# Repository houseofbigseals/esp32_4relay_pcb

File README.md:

KOLOS is an automation module based on ESP32-S3, designed for remote control of laboratory equipment - AC devices, sensors, indicators. Designed to manage environmental control systems for laboratory greenhouses with higher plants.  

Designed on a 4-layer printed circuit board, has dimensions of 124x95 mm.  
Powered by 5V via USB-C or screw connector, it has built-in surge protection with a self-resetting fuse. ESP32 is powered by a built-in AMS-1117-3.3 stabilizer.  
The board has expansion pins for connecting additional equipment to the controller, as well as screw connectors for connecting sensors using the 1-Wire protocol. The firmware of the controller and communication with the PC is done through the built-in USB-UART converter CP2102N. The board contains four relay channels controlled via an optocoupler and an HDC1080 temperature-humidity sensor.  
Mounting can be done in the housing with M3 screws or on a DIN rail, for which fasteners are provided.  
The firmware is implemented on the basis of the ESP-HOME framework for integrating the product into the Home Assistant environment. The system is configured so that the user can securely access the board remotely, via a Wireguard network, or locally.  

The pcb contains:  
- 4 5v relay module
- buttons for manual switching of the relay state in an emergency situation  
- optocoupler for relay control from the controller
- AMS-1117-3.3.
- USB-UART converter CP2102N.
- USB type-c for power and connection to a PC
- expansion pins for ESP32
- temperature-humidity sensor HDC1080
- expansion pins for connecting sensors via 1-Wire

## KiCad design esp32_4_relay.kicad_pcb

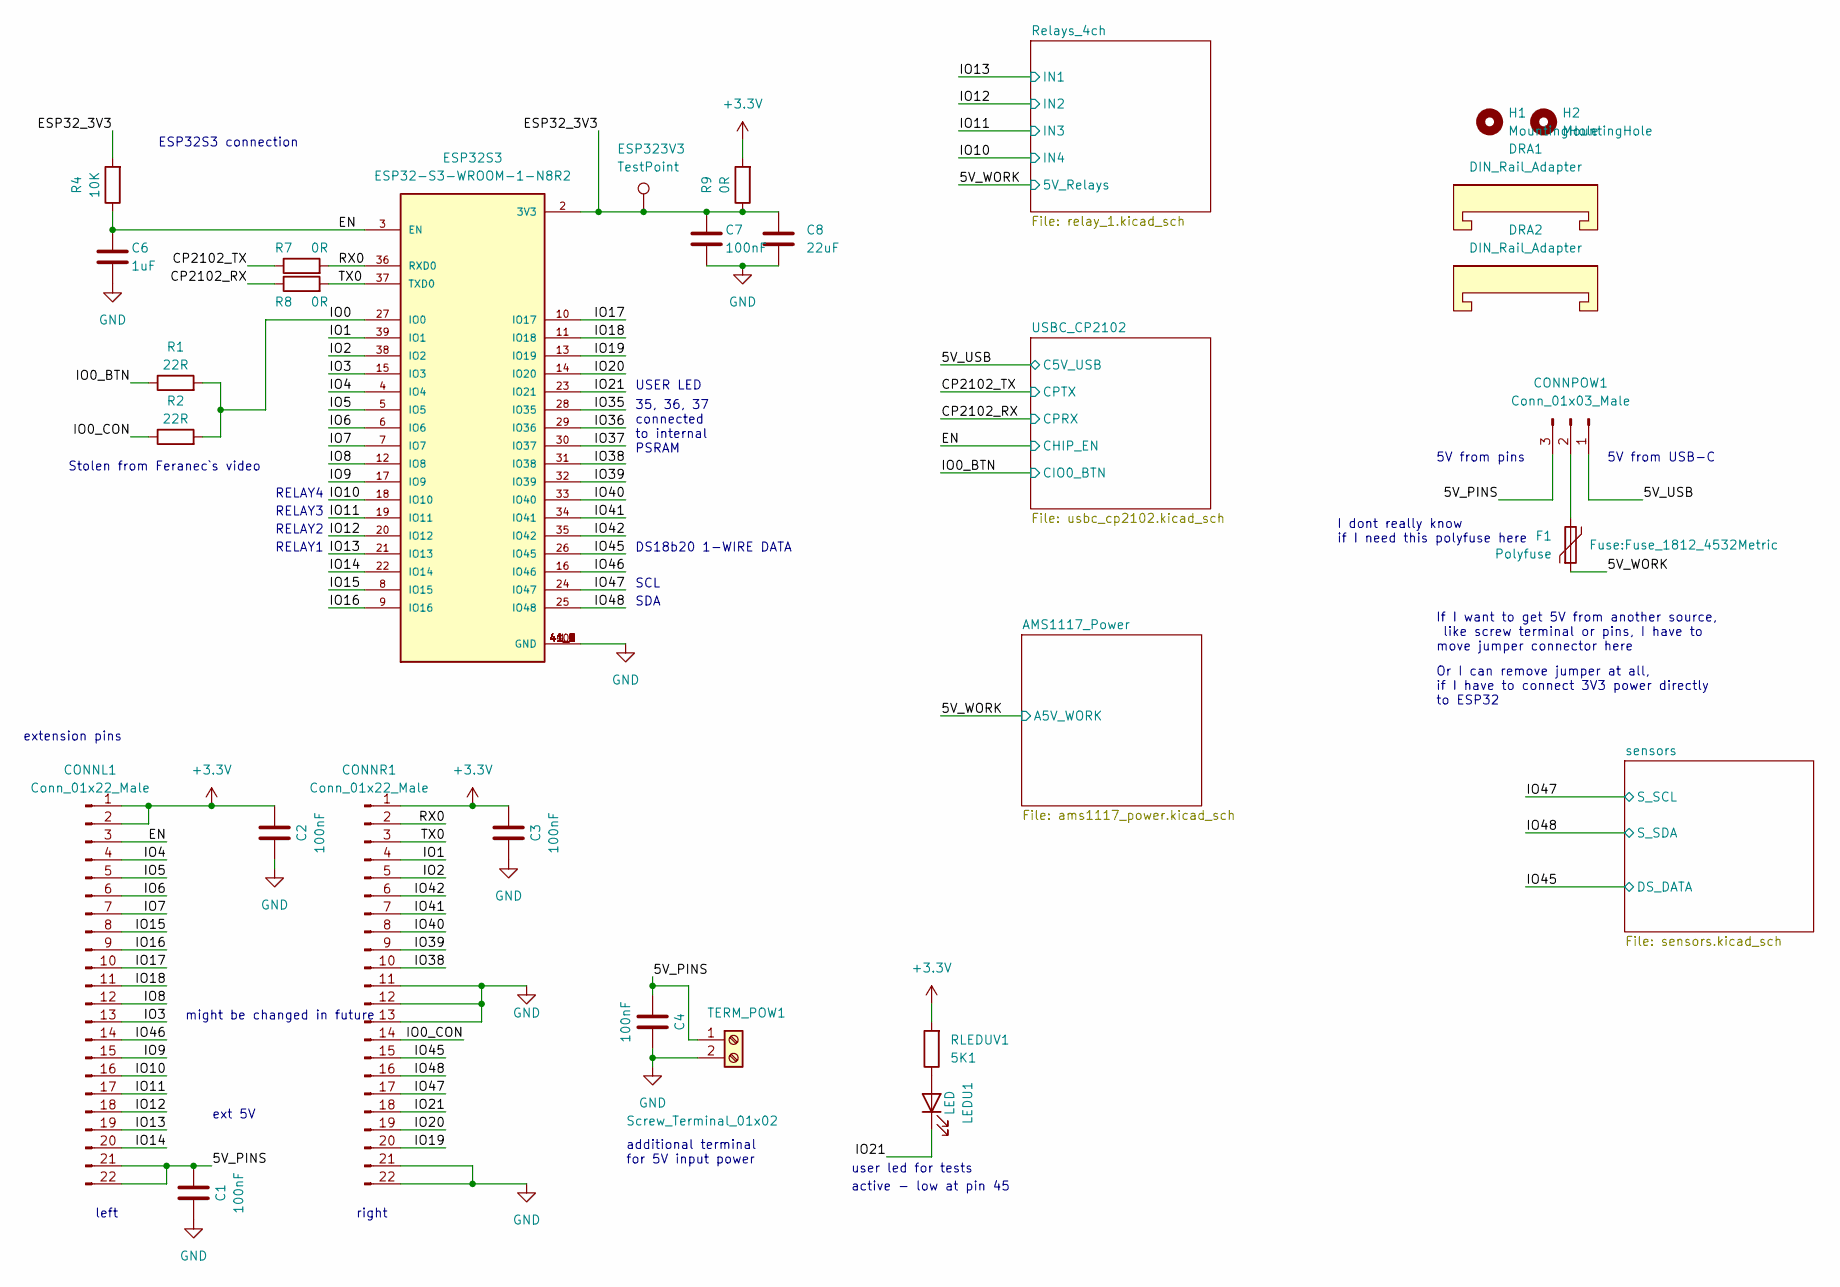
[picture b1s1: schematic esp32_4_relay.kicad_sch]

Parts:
C1, C2, C3, C4, C7: 100nF; C_0805_2012Metric
C6: 1uF; C_0805_2012Metric
C8: 22uF; C_0805_2012Metric
CONNL1: Conn_01x22_Male; PinHeader_1x22_P2.54mm_Vertical
CONNPOW1: Conn_01x03_Male; PinHeader_1x03_P2.54mm_Vertical
CONNR1: Conn_01x22_Male; PinHeader_1x22_P2.54mm_Vertical
DRA1, DRA2: DIN_Rail_Adapter; DINRailAdapter_3xM3_PhoenixContact_1201578
ESP32S3: ESP32-S3-WROOM-1-N8R2; XCVR_ESP32-S3-WROOM-1-N8R2; PARTREV v1.0; LCSC C2913204
ESP323V3: TestPoint; TestPoint_Pad_2.0x2.0mm
F1: Polyfuse; Fuse_1812_4532Metric; LCSC C84140
H1, H2: MountingHole; MountingHole_3.2mm_M3_DIN965
LEDU1: LED; LED_0805_2012Metric
R1, R2: 22R; R_0805_2012Metric
R4: 10K; R_0805_2012Metric
R7, R8, R9: 0R; R_0805_2012Metric
RLEDUV1: 5K1; R_0805_2012Metric
TERM_POW1: Screw_Terminal_01x02; Screw-2-pin-conn

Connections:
+3.3V: C2.2, C3.2, CONNL1.1, CONNL1.2, CONNR1.1, R9.2, RLEDUV1.2; also elsewhere on the board
/5V_PINS: C1.2, C4.2, CONNL1.21, CONNL1.22, CONNPOW1.3, TERM_POW1.1
/5V_USB: CONNPOW1.1; also elsewhere on the board
/5V_WORK: F1.1; also elsewhere on the board
/CP2102_RX: R8.1; also elsewhere on the board
/CP2102_TX: R7.1; also elsewhere on the board
/EN: C6.1, CONNL1.3, ESP32S3.3 (EN), R4.1; also elsewhere on the board
/ESP32_3V3: C7.1, C8.1, ESP32S3.2 (3V3), ESP323V3.1, R4.2, R9.1
/IO0: ESP32S3.27 (IO0), R1.2, R2.2
/IO0_BTN: R1.1; also elsewhere on the board
/IO0_CON: CONNR1.14, R2.1
/IO1: CONNR1.4, ESP32S3.39 (IO1)
/IO2: CONNR1.5, ESP32S3.38 (IO2)
/IO3: CONNL1.13, ESP32S3.15 (IO3)
/IO4: CONNL1.4, ESP32S3.4 (IO4)
/IO5: CONNL1.5, ESP32S3.5 (IO5)
/IO6: CONNL1.6, ESP32S3.6 (IO6)
/IO7: CONNL1.7, ESP32S3.7 (IO7)
/IO8: CONNL1.12, ESP32S3.12 (IO8)
/IO9: CONNL1.15, ESP32S3.17 (IO9)
/IO10: CONNL1.16, ESP32S3.18 (IO10); also elsewhere on the board
/IO11: CONNL1.17, ESP32S3.19 (IO11); also elsewhere on the board
/IO12: CONNL1.18, ESP32S3.20 (IO12); also elsewhere on the board
/IO13: CONNL1.19, ESP32S3.21 (IO13); also elsewhere on the board
/IO14: CONNL1.20, ESP32S3.22 (IO14)
/IO15: CONNL1.8, ESP32S3.8 (IO15)
/IO16: CONNL1.9, ESP32S3.9 (IO16)
/IO17: CONNL1.10, ESP32S3.10 (IO17)
/IO18: CONNL1.11, ESP32S3.11 (IO18)
/IO19: CONNR1.20, ESP32S3.13 (IO19)
/IO20: CONNR1.19, ESP32S3.14 (IO20)
/IO21: CONNR1.18, ESP32S3.23 (IO21), LEDU1.1 (K)
/IO35: ESP32S3.28 (IO35)
/IO36: ESP32S3.29 (IO36)
/IO37: ESP32S3.30 (IO37)
/IO38: CONNR1.10, ESP32S3.31 (IO38)
/IO39: CONNR1.9, ESP32S3.32 (IO39)
/IO40: CONNR1.8, ESP32S3.33 (IO40)
/IO41: CONNR1.7, ESP32S3.34 (IO41)
/IO42: CONNR1.6, ESP32S3.35 (IO42)
/IO45: CONNR1.15, ESP32S3.26 (IO45); also elsewhere on the board
/IO46: CONNL1.14, ESP32S3.16 (IO46)
/IO47: CONNR1.17, ESP32S3.24 (IO47); also elsewhere on the board
/IO48: CONNR1.16, ESP32S3.25 (IO48); also elsewhere on the board
/RX0: CONNR1.2, ESP32S3.36 (RXD0), R7.2
/TX0: CONNR1.3, ESP32S3.37 (TXD0), R8.2
GND: C1.1, C2.1, C3.1, C4.1, C6.2, C7.2, C8.2, CONNR1.11, CONNR1.12, CONNR1.13, CONNR1.21, CONNR1.22, ESP32S3.1 (GND), ESP32S3.40 (GND), ESP32S3.41_1 (GND), ESP32S3.41_2 (GND), ESP32S3.41_3 (GND), ESP32S3.41_4 (GND), ESP32S3.41_5 (GND), ESP32S3.41_6 (GND), ESP32S3.41_7 (GND), ESP32S3.41_8 (GND), ESP32S3.41_9 (GND), TERM_POW1.2; also elsewhere on the board
unnamed: CONNPOW1.2, F1.2
unnamed: LEDU1.2 (A), RLEDUV1.1

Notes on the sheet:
ESP32S3 connection
left
5V from pins
5V from USB-C
Or I can remove jumper at all, if I have to connect 3V3 power directly to ESP32
might be changed in future
extension pins
35, 36, 37 connected to internal PSRAM
user led for tests
SCL
SDA
ext 5V
I dont really know if I need this polyfuse here
USER LED
RELAY2
right
additional terminal for 5V input power
RELAY1
active - low at pin 45
RELAY4
DS18b20 1-WIRE DATA
Stolen from Feranec`s video
If I want to get 5V from another source, like screw terminal or pins, I have to move jumper connector here
RELAY3

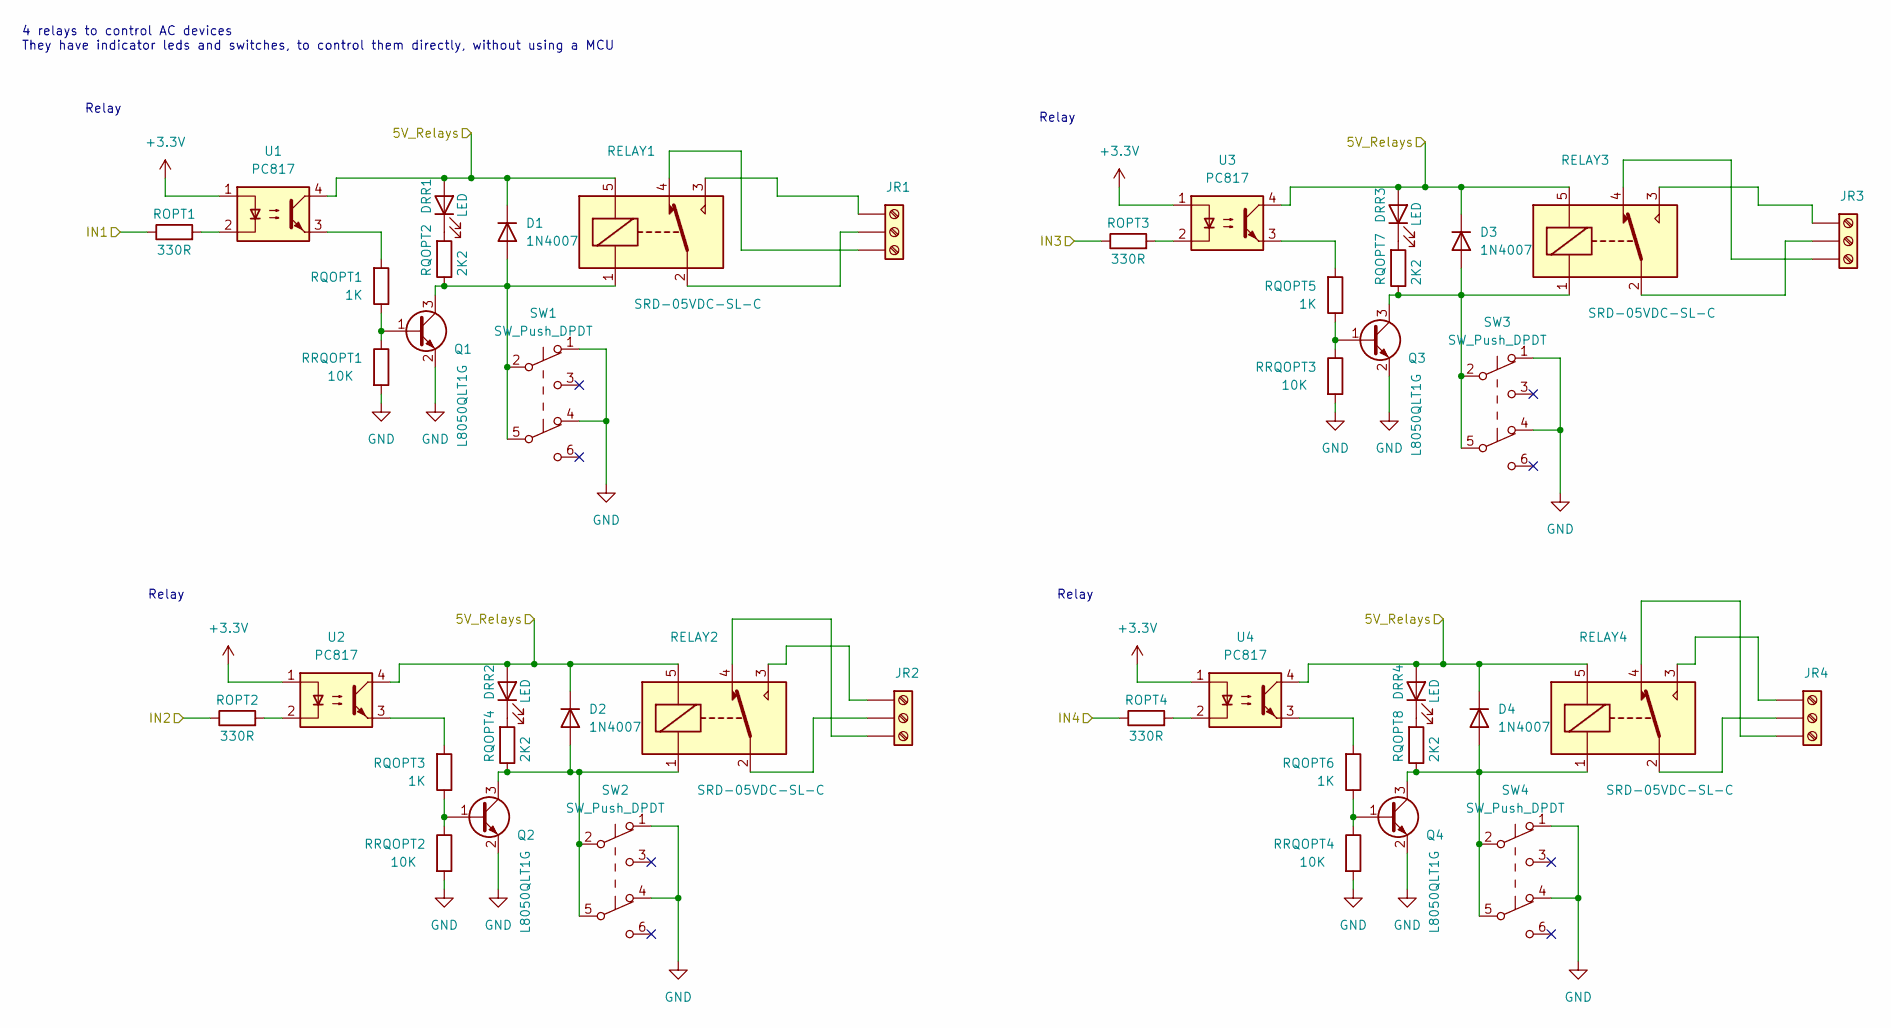
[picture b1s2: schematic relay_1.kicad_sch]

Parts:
D1, D2, D3, D4: 1N4007; D_SMA
DRR1, DRR2, DRR3, DRR4: LED; LED_0805_2012Metric
JR1, JR2, JR3, JR4: Screw_Terminal_01x03; Screw-3-pin-conn
Q1, Q2, Q3, Q4: L8050QLT1G; SOT-23
RELAY1, RELAY2, RELAY3, RELAY4: SRD-05VDC-SL-C; Relay_T75
ROPT1, ROPT2, ROPT3, ROPT4: 330R; R_0805_2012Metric
RQOPT1, RQOPT3, RQOPT5, RQOPT6: 1K; R_0805_2012Metric
RQOPT2, RQOPT4, RQOPT7, RQOPT8: 2K2; R_0805_2012Metric
RRQOPT1, RRQOPT2, RRQOPT3, RRQOPT4: 10K; R_0805_2012Metric
SW1, SW2, SW3, SW4: SW_Push_DPDT; switch-dpdt
U1, U2, U3, U4: PC817; SOP-4_3.8x4.1mm_P2.54mm

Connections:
+3.3V: U1.1, U2.1, U3.1, U4.1; also elsewhere on the board
/5V_WORK: D1.1 (K), D2.1 (K), D3.1 (K), D4.1 (K), DRR1.2 (A), DRR2.2 (A), DRR3.2 (A), DRR4.2 (A), RELAY1.5, RELAY2.5, RELAY3.5, RELAY4.5, U1.4, U2.4, U3.4, U4.4; also elsewhere on the board
/IO10: ROPT4.1; also elsewhere on the board
/IO11: ROPT3.1; also elsewhere on the board
/IO12: ROPT2.1; also elsewhere on the board
/IO13: ROPT1.1; also elsewhere on the board
GND: Q1.2 (E), Q2.2 (E), Q3.2 (E), Q4.2 (E), RRQOPT1.2, RRQOPT2.2, RRQOPT3.2, RRQOPT4.2, SW1.1 (A), SW1.4 (A), SW2.1 (A), SW2.4 (A), SW3.1 (A), SW3.4 (A), SW4.1 (A), SW4.4 (A); also elsewhere on the board
unnamed: D1.2 (A), Q1.3 (C), RELAY1.1, RQOPT2.1, SW1.2 (B), SW1.5 (B)
unnamed: D2.2 (A), Q2.3 (C), RELAY2.1, RQOPT4.1, SW2.2 (B), SW2.5 (B)
unnamed: D3.2 (A), Q3.3 (C), RELAY3.1, RQOPT7.1, SW3.2 (B), SW3.5 (B)
unnamed: D4.2 (A), Q4.3 (C), RELAY4.1, RQOPT8.1, SW4.2 (B), SW4.5 (B)
unnamed: DRR1.1 (K), RQOPT2.2
unnamed: DRR2.1 (K), RQOPT4.2
unnamed: DRR3.1 (K), RQOPT7.2
unnamed: DRR4.1 (K), RQOPT8.2
unnamed: JR1.1, RELAY1.3
unnamed: JR1.2, RELAY1.2
unnamed: JR1.3, RELAY1.4
unnamed: JR2.1, RELAY2.3
unnamed: JR2.2, RELAY2.2
unnamed: JR2.3, RELAY2.4
unnamed: JR3.1, RELAY3.3
unnamed: JR3.2, RELAY3.2
unnamed: JR3.3, RELAY3.4
unnamed: JR4.1, RELAY4.3
unnamed: JR4.2, RELAY4.2
unnamed: JR4.3, RELAY4.4
unnamed: Q1.1 (B), RQOPT1.1, RRQOPT1.1
unnamed: Q2.1 (B), RQOPT3.1, RRQOPT2.1
unnamed: Q3.1 (B), RQOPT5.1, RRQOPT3.1
unnamed: Q4.1 (B), RQOPT6.1, RRQOPT4.1
unnamed: ROPT1.2, U1.2
unnamed: ROPT2.2, U2.2
unnamed: ROPT3.2, U3.2
unnamed: ROPT4.2, U4.2
unnamed: RQOPT1.2, U1.3
unnamed: RQOPT3.2, U2.3
unnamed: RQOPT5.2, U3.3
unnamed: RQOPT6.2, U4.3

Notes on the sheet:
Relay
4 relays to control AC devices They have indicator leds and switches, to control them directly, without using a MCU

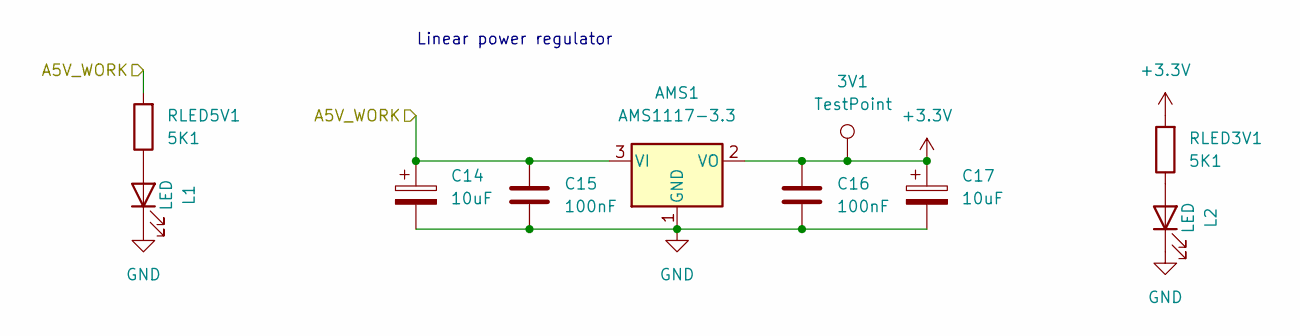
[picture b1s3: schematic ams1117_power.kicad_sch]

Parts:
3V1: TestPoint; TestPoint_Pad_2.0x2.0mm
AMS1: AMS1117-3.3; SOT-223-3_TabPin2
C14, C17: 10uF; CP_Radial_D10.0mm_P5.00mm
C15, C16: 100nF; C_0805_2012Metric
L1, L2: LED; LED_0805_2012Metric
RLED3V1, RLED5V1: 5K1; R_0805_2012Metric

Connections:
+3.3V: 3V1.1, AMS1.2 (VO), C16.1, C17.1, RLED3V1.2; also elsewhere on the board
/5V_WORK: AMS1.3 (VI), C14.1, C15.1, RLED5V1.2; also elsewhere on the board
GND: AMS1.1 (GND), C14.2, C15.2, C16.2, C17.2, L1.1 (K), L2.1 (K); also elsewhere on the board
unnamed: L1.2 (A), RLED5V1.1
unnamed: L2.2 (A), RLED3V1.1

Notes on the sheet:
Linear power regulator

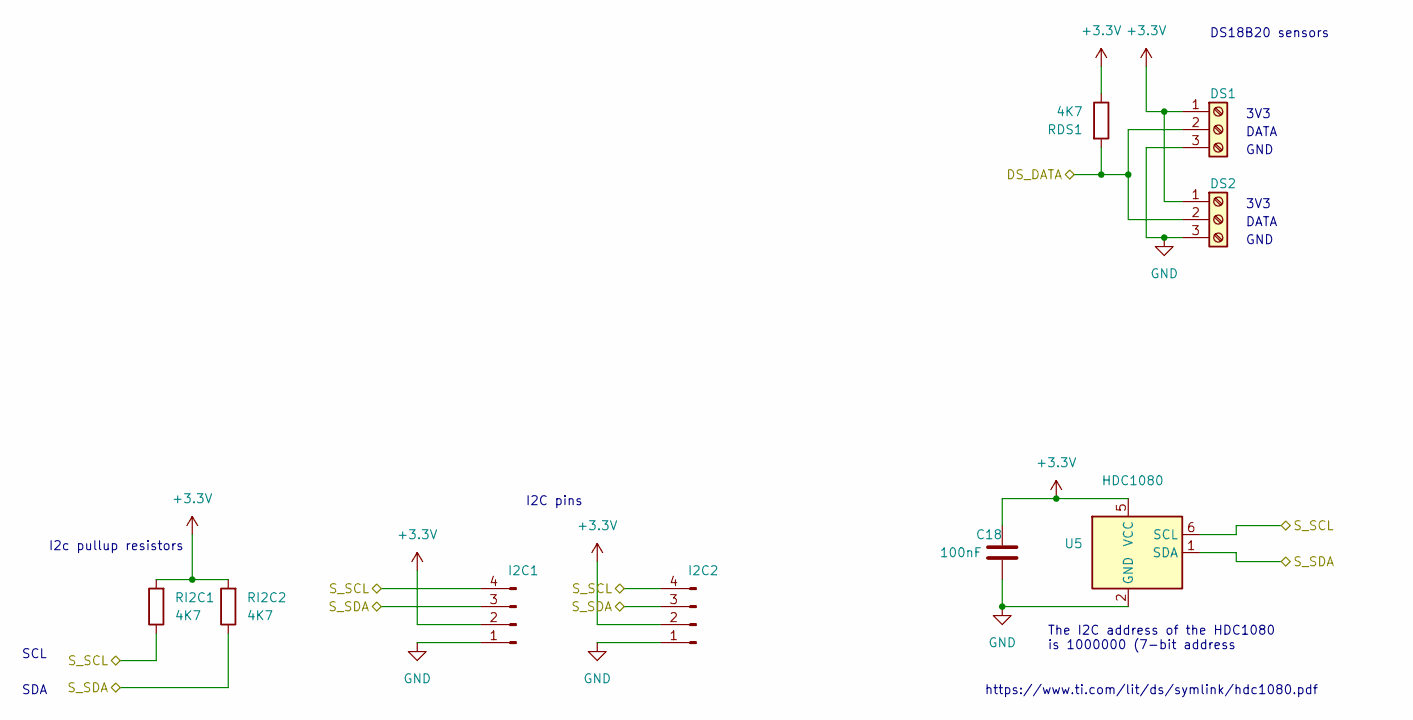
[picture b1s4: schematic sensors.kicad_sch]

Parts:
C18: 100nF; C_0805_2012Metric; LCSC C49678
DS1, DS2: Screw_Terminal_01x03; Screw-3-pin-conn
I2C1, I2C2: Conn_01x04_Male; PinHeader_1x04_P2.54mm_Vertical
RDS1: 4K7; R_0805_2012Metric
RI2C1, RI2C2: 4K7; R_0805_2012Metric
U5: HDC1080; Texas_PWSON-N6; LCSC C82227

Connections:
+3.3V: C18.1, DS1.1, DS2.1, I2C1.2, I2C2.2, RDS1.1, RI2C1.2, RI2C2.2, U5.5 (VCC); also elsewhere on the board
/IO45: DS1.2, DS2.2, RDS1.2; also elsewhere on the board
/IO47: I2C1.4, I2C2.4, RI2C1.1, U5.6 (SCL); also elsewhere on the board
/IO48: I2C1.3, I2C2.3, RI2C2.1, U5.1 (SDA); also elsewhere on the board
GND: C18.2, DS1.3, DS2.3, I2C1.1, I2C2.1, U5.2 (GND); also elsewhere on the board

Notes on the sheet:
GND
SCL
I2c pullup resistors
DATA
3V3
https://www.ti.com/lit/ds/symlink/hdc1080.pdf
I2C pins
SDA
The I2C address of the HDC1080 is 1000000 (7-bit address
DS18B20 sensors

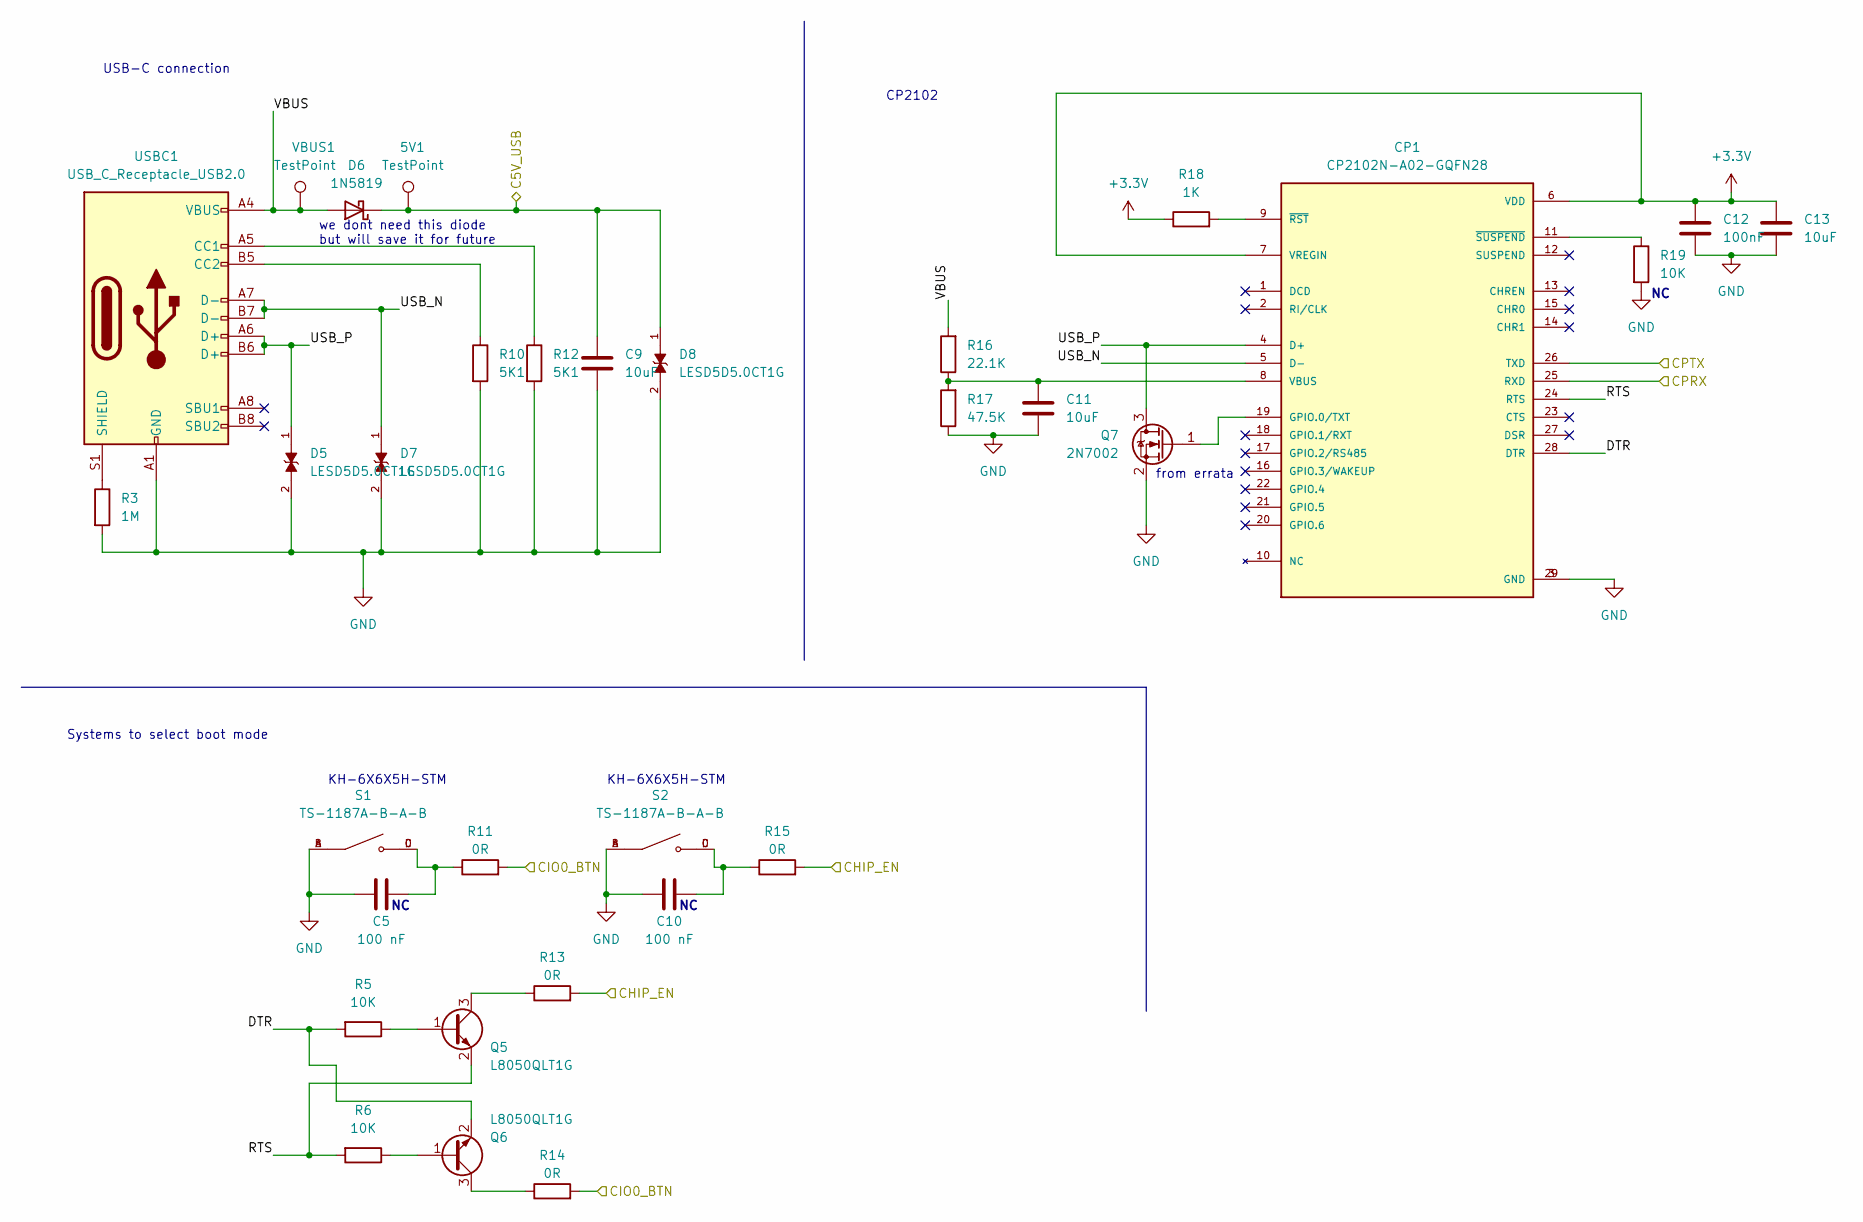
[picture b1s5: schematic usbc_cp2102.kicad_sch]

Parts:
5V1: TestPoint; TestPoint_Pad_2.0x2.0mm
C5, C10: 100 nF; C_0805_2012Metric
C9, C11, C13: 10uF; C_0805_2012Metric
C12: 100nF; C_0805_2012Metric
CP1: CP2102N-A02-GQFN28; QFN50P500X500X80-29N; PARTREV 1.5
D5, D7, D8: LESD5D5.0CT1G; TVS_LESD5D5.0CT1G; PARTREV O
D6: 1N5819; D_SMA
Q5, Q6: L8050QLT1G; SOT-23
Q7: 2N7002; SOT-23
R3: 1M; R_0805_2012Metric
R5, R6, R19: 10K; R_0805_2012Metric
R10, R12: 5K1; R_0805_2012Metric
R11, R13, R14, R15: 0R; R_0805_2012Metric
R16: 22.1K; R_0805_2012Metric
R17: 47.5K; R_0805_2012Metric
R18: 1K; R_0805_2012Metric
S1, S2: TS-1187A-B-A-B; SW_TS-1187A-B-A-B; PARTREV A0
USBC1: USB_C_Receptacle_USB2.0; USB_C_Receptacle_HRO_TYPE-C-31-M-12
VBUS1: TestPoint; TestPoint_Pad_2.0x2.0mm

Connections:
+3.3V: C12.1, C13.1, CP1.6 (VDD), CP1.7 (VREGIN), R18.1; also elsewhere on the board
/5V_USB: 5V1.1, C9.1, D6.1 (K), D8.1; also elsewhere on the board
/CP2102_RX: CP1.25 (RXD); also elsewhere on the board
/CP2102_TX: CP1.26 (TXD); also elsewhere on the board
/EN: R13.2, R15.2; also elsewhere on the board
/IO0_BTN: R11.2, R14.2; also elsewhere on the board
/USBC_CP2102/DTR: CP1.28 (DTR), Q6.2 (E), R5.2
/USBC_CP2102/RTS: CP1.24 (RTS), Q5.2 (E), R6.2
/USBC_CP2102/USB_N: CP1.5 (D-), D7.1, USBC1.A7 (D-), USBC1.B7 (D-)
/USBC_CP2102/USB_P: CP1.4 (D+), D5.1, Q7.3 (D), USBC1.A6 (D+), USBC1.B6 (D+)
/USBC_CP2102/VBUS: D6.2 (A), R16.2, USBC1.A4 (VBUS), USBC1.A9 (VBUS), USBC1.B4 (VBUS), USBC1.B9 (VBUS), VBUS1.1
GND: C5.1, C9.2, C10.1, C11.2, C12.2, C13.2, CP1.3 (GND), CP1.29 (GND), D5.2, D7.2, D8.2, Q7.2 (S), R3.2, R10.2, R12.2, R17.1, R19.2, S1.A, S1.B, S2.A, S2.B, USBC1.A1 (GND), USBC1.A12 (GND), USBC1.B1 (GND), USBC1.B12 (GND); also elsewhere on the board
unnamed: C5.2, R11.1, S1.C, S1.D
unnamed: C10.2, R15.1, S2.C, S2.D
unnamed: C11.1, CP1.8 (VBUS), R16.1, R17.2
unnamed: CP1.9 (~RST), R18.2
unnamed: CP1.11 (~SUSPEND), R19.1
unnamed: CP1.19 (GPIO.0/TXT), Q7.1 (G)
unnamed: Q5.1 (B), R5.1
unnamed: Q5.3 (C), R13.1
unnamed: Q6.1 (B), R6.1
unnamed: Q6.3 (C), R14.1
unnamed: R3.1, USBC1.S1 (SHIELD)
unnamed: R10.1, USBC1.B5 (CC2)
unnamed: R12.1, USBC1.A5 (CC1)

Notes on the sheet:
USB-C connection
KH-6X6X5H-STM
from errata
we dont need this diode but will save it for future
CP2102
Systems to select boot mode

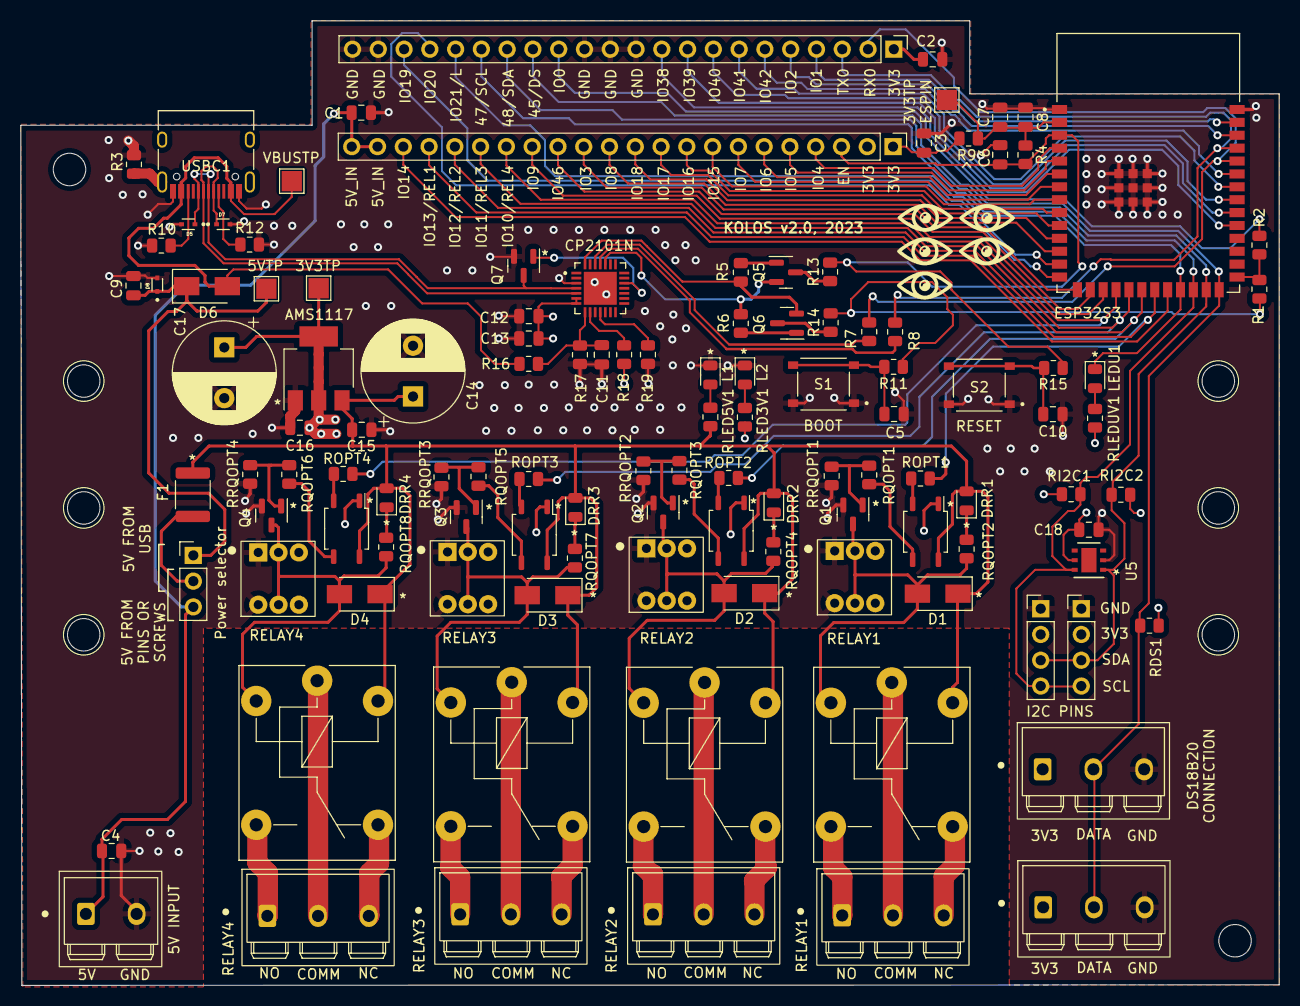
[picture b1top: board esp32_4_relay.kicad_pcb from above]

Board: 4 copper layers, 124.0 x 95.0 mm, 121 parts (0 on the bottom side), 98 nets.

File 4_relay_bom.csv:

Designator,Footprint,Quantity,Value,LCSC Part #
AMS1,SOT-223-3_TabPin2,1,AMS1117-3.3,C6186
"C1, C12, C15, C16, C18, C2, C3, C4, C7",805,9,100nF,C49678
"C11, C13, C9",805,3,10uF,C440198
C6,805,1,1uF,C28323
C8,805,1,22uF,C45783
CP1,QFN50P500X500X80-29N,1,CP2102N-A02-GQFN28,C964632
"D1, D2, D3, D4",D_SMA,4,1N4007,C95872
"D5, D7, D8",TVS_LESD5D5.0CT1G,3,LESD5D5.0CT1G,C383211
D6,D_SMA,1,1N5819,C191023
"DRR1, DRR2, DRR3, DRR4, L1, L2, LEDU1",805,7,LED,C84256
"DS1, DS2, JR1, JR2, JR3, JR4",Screw-3-pin-conn,6,Screw_Terminal_01x03,C784923
ESP32S3,XCVR_ESP32-S3-WROOM-1-N8R2,1,ESP32-S3-WROOM-1-N8R2,C2913204
F1,1812,1,Polyfuse,C84140
"Q1, Q2, Q3, Q4, Q5, Q6",SOT-23,6,L8050QLT1G,C8512 
Q7,SOT-23,1,2N7002,C8545
"R1, R2",805,2,22R,C17561
"R10, R12, RLED3V1, RLED5V1, RLEDUV1",805,5,5K1,C27834
"R11, R13, R14, R15, R7, R8, R9",805,7,0R,C17477
R16,805,1,22.1K,C17560
R17,805,1,47.5K,C17713
"R18, RQOPT1, RQOPT3, RQOPT5, RQOPT6",805,5,1K,C17513
R3,805,1,1M,C17514
"R4, R5, R6",805,3,10K,C17414
"RDS1, RI2C1, RI2C2",805,3,4K7,C17673
"RELAY1, RELAY2, RELAY3, RELAY4",Relay_T75,4,SRD-05VDC-SL-C,C35449
"ROPT1, ROPT2, ROPT3, ROPT4",805,4,330R,C17630
"RQOPT2, RQOPT4, RQOPT7, RQOPT8",805,4,2K2,C17520
"S1, S2",SW_TS-1187A-B-A-B,2,TS-1187A-B-A-B,C318884
"SW1, SW2, SW3, SW4",switch-dpdt,4,SW_Push_DPDT,C318862
TERM_POW1,Screw-2-pin-conn,1,Screw_Terminal_01x02,C784922
"U1, U2, U3, U4",SOP-4_3.8x4.1mm_P2.54mm,4,PC817,C6649
U5,Texas_PWSON-N6,1,HDC1080,C82227
USBC1,USB_C_Receptacle_HRO_TYPE-C-31-M-12,1,USB_C_Receptacle_USB2.0,C165948

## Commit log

2023-04-19 initial
2023-04-27 pre-production
2023-05-03 new pre-fabrication
2023-05-04 production
2023-05-17 add readme
2023-06-03 fix cp2102 transistor
